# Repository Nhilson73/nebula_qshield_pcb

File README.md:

# Nebula Q-Shield® PCB

**Precision Fermentation Monitor** — PCB shield de 4 capas para el Arduino UNO Q, con sensores de fermentación, control de actuadores, HMI UART y trazabilidad integrada al ecosistema Nebula.

Built by [Cafelium SRL](https://github.com/Nhilson73) · Dominican Republic

> **Parte del ecosistema [Nebula Q-Shield — Arduino App Lab](https://github.com/Nhilson73/Nebula_ArduinoAPPLab_UNOQ)**
>
> **Awards:** I+D Lab INDOTEL 2025 · CREE Banreservas 2026 · Pitch4FUN 2026
>
> **Firmware source of truth:** [`Nhilson73/Nebula_ArduinoAPPLab_UNOQ`](https://github.com/Nhilson73/Nebula_ArduinoAPPLab_UNOQ). No usar `Nebula_UNOQ_ArduinoIDE_Core` para validaciones de pinout/hardware.
>
> **Estado actual (2026-08-12):** esquemático validado (ERC 0 violaciones), PCB en KiCad 10.0.5, factor de forma UNO Q inmutable, dimensiones **150 mm × 120 mm** (se amplió el ancho para la propuesta de placement de Gemini Spark), Fase 4 de potencia completa y Fase 5/6 de ruteo en progreso: DRC 0 violaciones, 72 nets desconectados restantes. Se ajustó `Signal_Default` a vía mínima 0.5/0.2 mm para mejorar conectividad GND. Ver `docs/INSIGHT_FABRICATION_ROADMAP.md`.

---

## ¿Qué es el Q-Shield®?

El Q-Shield® es un **PCB shield de 4 capas** que se monta sobre el Arduino UNO Q (STM32U585 MCU + Qualcomm QRB2210 MPU), convirtiendo la placa en un sistema completo de monitoreo y control de fermentación para café y cacao de especialidad.

Se fabrica como **una sola PCB** para los tres tiers. La diferencia entre tiers se logra poblando o dejando en DNP ciertos componentes; el firmware selecciona el tier en tiempo de compilación.

```
┌──────────────────────────────────────────────────────────────────┐
│                    NEBULA Q-SHIELD® PCB v1.0                     │
│                                                                  │
│  ┌──────────────┐  ┌──────────────┐  ┌──────────────────────┐   │
│  │ POTENCIA     │  │  ANALÓGICO    │  │     DIGITAL          │   │
│  │              │  │              │  │                      │   │
│  │ 12 V input   │  │ pH  (A0)     │  │ I2C bus (D20/D21)    │   │
│  │ Buck 12→5 V  │  │ ORP (A1)     │  │ HX711 (D2/D3)        │   │
│  │ LDO 5→3.3 V  │  │ Temp (A2)    │  │ GPS + RTC (I2C)      │   │
│  │ TVS + PTC    │  │ CO2 (A4)     │  │ RS485 bridge (Sig.)  │   │
│  │ Schottky     │  │ DO  (A5)     │  │ HMI UART             │   │
│  └──────────────┘  └──────────────┘  └──────────────────────┘   │
│                                                                  │
│  ┌──────────────────────────────────────────────────────────┐   │
│  │  ACTUADORES (opto-aislados) — Insight+                  │   │
│  │  Recirculación · Solenoide gas · Chiller                 │   │
│  └──────────────────────────────────────────────────────────┘   │
│                                                                  │
│  ┌──────────────────────────────────────────────────────────┐   │
│  │  CONECTOR ARDUINO UNO Q / R3 (32-pin shield header)      │   │
│  └──────────────────────────────────────────────────────────┘   │
└──────────────────────────────────────────────────────────────────┘
```

---

## Hardware Tier Model

Una sola PCB para los 3 tiers — los componentes no poblados (DNP) se seleccionan en fabricación:

| Tier | Sensores / Funciones | Actuadores | Placements poblados |
|------|----------------------|-----------|---------------------|
| **Essential®** | GPS (altitud), RTC/timestamp, temperatura, pH, ORP, HMI | — | 88 / 163 |
| **Insight®** | Essential + CO₂ (presión), DO, celdas de carga, I2C bus D20/D21 | Recirculación, solenoide gas, chiller | 137 / 163 |
| **Signature®** | Insight + densidad celular total (TCD) + activa (ACD) Hamilton vía RS485 | Igual que Insight | 146 / 163 |

- Convención DNP en el campo `DNP`: lista los tiers en los que el componente **no** se pobla.
- Canal de humedad y válvula PWM de gas quedan eliminados/DNP en todos los tiers.
- El pinout detallado de `J21` está en `docs/INSIGHT_FABRICATION_ROADMAP.md`.

---

## Componentes principales

| # | Componente | Interfaz | Tier |
|---|-----------|----------|------|
| 1 | Sensor pH | Analógico A0 / I2C EZO | Essential+ |
| 2 | Sensor ORP | Analógico A1 / I2C EZO | Essential+ |
| 3 | Sensor temperatura | Analógico A2 | Essential+ |
| 4 | GPS u-blox SAM-M8Q (altitud por GPS) | I2C 0x42 | Essential+ |
| 5 | RTC DS3231 | I2C 0x68 | Essential+ |
| 6 | HMI UART 5" (Nextion/Stone/DWIN) | UART TX/RX | Todos |
| 7 | Celdas de carga + HX711 | Digital D2/D3 | Insight+ |
| 8 | Transductor presión CO₂ | Analógico A4 | Insight+ |
| 9 | Sensor oxígeno disuelto (DO) | Analógico A5 | Insight+ |
| 10 | Driver recirculación (half-bridge) | PWM/DIR D5/D6 | Insight+ |
| 11 | Solenoide gas CO₂/H₂ | GPIO D7 | Insight+ |
| 12 | Chiller (relé opto-aislado) | GPIO D8 | Insight+ |
| 13 | Sensores Hamilton TCD + ACD | RS485/Modbus | Signature |

---

## Diseño 100% Foolproof — 7 Capas de Protección

```
┌─────────────────────────────────────────────────────────┐
│  7. Firmware failsafe (watchdog, store-forward)         │
│  ┌─────────────────────────────────────────────────┐   │
│  │  6. Aislamiento galvánico (ISO7721, PC817)      │   │
│  │  ┌─────────────────────────────────────────┐   │   │
│  │  │  5. Protección térmica (shutdown auto)  │   │   │
│  │  │  ┌─────────────────────────────────┐   │   │   │
│  │  │  │  4. Limitación corriente (PTC)  │   │   │   │
│  │  │  │  ┌─────────────────────────┐   │   │   │   │
│  │  │  │  │  3. ESD/TVS (±8kV)      │   │   │   │   │
│  │  │  │  │  ┌─────────────────┐   │   │   │   │   │
│  │  │  │  │  │  2. Polaridad   │   │   │   │   │   │
│  │  │  │  │  │  ┌─────────┐   │   │   │   │   │   │
│  │  │  │  │  │  │1. Mecán.│   │   │   │   │   │   │
│  │  │  │  │  │  └─────────┘   │   │   │   │   │   │
│  │  │  │  │  └─────────────────┘   │   │   │   │   │
│  │  │  │  └─────────────────────────┘   │   │   │   │
│  │  │  └─────────────────────────────────┘   │   │   │
│  │  └─────────────────────────────────────────┘   │   │
│  └─────────────────────────────────────────────────┘   │
└─────────────────────────────────────────────────────────┘
```

- **Conectores keyed** — Físicamente imposible conectar al revés
- **Schottky SS34** — Protección polaridad inversa sin daño
- **TVS ESD IEC 61000-4-2 Level 4** — ±8 kV contacto, ±15 kV aire
- **PTC recuperable** — Auto-reset después de cortocircuito
- **Thermal shutdown** — Reguladores se apagan a 85°C y se recuperan
- **Opto-aislamiento** — MCU aislado de actuadores de potencia
- **Watchdog dual** — TPS3823 externo (1.6s) + IWDG interno (8s), poblado en TODOS los tiers
- **Aislamiento galvánico on-board** — SN6501 + AMC1301/ISO1541 por canal húmedo (pH, ORP, DO)

---

## Cumplimiento Normativo Europeo

| Directiva | Norma | Estado |
|-----------|-------|--------|
| **EMC** (2014/30/EU) | EN 55032 Clase B, EN 61000-4-2/3/4/5/6 | Diseñado |
| **RoHS 3** (2011/65/EU + 2015/863) | Soldadura SAC305, ENIG, sin Pb/Hg/Cd | Especificado |
| **WEEE** (2012/19/EU) | Categoría 6, registro por país | Pendiente registro |
| **RED** (2014/53/EU) | WiFi/BT via Arduino UNO Q cert. | Verificar con Arduino |
| **REACH** ((EC) 1907/2006) | Verificación SVHC proveedores | Pendiente |
| **Marcado CE** | Declaración de Conformidad | Post-ensayos |

---

## Estructura del Repositorio

```
nebula_qshield_pcb/
├── README.md                          # Este documento
├── .gitignore                         # Exclusiones KiCad/OS
│
├── docs/                              # Documentación de ingeniería
│   ├── 01_PCB_ARCHITECTURE.md         # Arquitectura completa del PCB
│   ├── 02_FOOLPROOF_DESIGN.md         # Diseño 100% Foolproof (7 capas)
│   ├── 03_EU_COMPLIANCE.md            # Cumplimiento normativo europeo
│   ├── 04_BOM_PRODUCTION.md           # BOM con part numbers Digi-Key/Mouser
│   ├── 05_POWER_BUDGET.md             # Análisis de presupuesto de potencia
│   ├── 06_PCB_LAYOUT_STACKUP.md       # Guías de layout y stackup 4 capas
│   ├── 07_KICAD_NETLIST.md            # Netlist KiCad y definiciones
│   ├── 08_MECHANICAL_ANALYSIS.md      # Análisis mecánico y compactación
│   ├── INSIGHT_FABRICATION_ROADMAP.md # Hoja de ruta JLCPCB para Insight
│   ├── UNO_Q_FORM_FACTOR.md           # Referencia inmutable del factor de forma UNO Q
│   ├── KICAD10_SSH_SETUP.md           # Guía SSH para clonar desde KiCad 10
│   └── DOCUMENTATION_UPDATE_AUDIT.md  # Auditoría de docs por actualizar
│
├── kicad/                             # Proyecto KiCad 10.0.5
│   ├── nebula_qshield.kicad_pro       # Proyecto principal
│   ├── nebula_qshield.kicad_sch       # Esquemático raíz (jerárquico)
│   ├── nebula_qshield.kicad_pcb       # Layout PCB (en progreso)
│   ├── power_management.kicad_sch     # Sub-hoja: reguladores y protección
│   ├── analog_acquisition.kicad_sch   # Sub-hoja: canales analógicos
│   ├── digital_i2c.kicad_sch          # Sub-hoja: bus I2C, HX711, RS485 bridge
│   ├── actuator_drivers.kicad_sch     # Sub-hoja: drivers de actuadores
│   ├── hmi_connectors.kicad_sch       # Sub-hoja: HMI UART y J21
│   ├── lib/                           # Librerías de símbolos y footprints
│   ├── production/                    # Salidas de fabricación
│   └── UNO_Q_rearchitecture_report.md # Reporte de re-arquitectura UNO Q
│
├── hardware/                          # Diseño mecánico
│   ├── enclosure/                     # Carcasa/enclosure IP54
│   └── cables/                        # Especificaciones de cables
│
├── test/                              # Testing y validación
│   ├── hil/                           # Hardware-in-the-Loop tests
│   └── validation/                    # Reportes de validación
│
└── tools/                             # Scripts Python de automatización
    ├── tier_counts.py                 # Conteos de componentes por tier
    ├── apply_tier_dnp4.py            # Aplicar propiedades DNP por tier
    ├── compare_pcb_to_netlist.py      # Verificar paridad PCB/netlist
    └── update_tier_comments.py       # Actualizar comentarios de tier
```

### Esquemáticos Jerárquicos

```
nebula_qshield.kicad_sch (raíz)
├── power_management.kicad_sch     → 12V protección, Buck 5V, LDO 3.3V, TPS3823 watchdog
├── analog_acquisition.kicad_sch   → pH/ORP/Temp/CO₂/DO + aislamiento galvánico
├── digital_i2c.kicad_sch          → I2C (D20/D21), HX711, RS485 Modbus bridge (Signature)
├── actuator_drivers.kicad_sch     → Recirculación, solenoide gas, chiller
└── hmi_connectors.kicad_sch       → HMI UART y shield header J21
```

---

## Especificaciones Técnicas

| Parámetro | Valor |
|-----------|-------|
| **Dimensiones** | 125 mm × 120 mm (factor de forma Arduino UNO Q inmutable; el tamaño exterior puede variar) |
| **Capas** | 4 (Signal–GND–Power–Signal) |
| **Material** | FR-4 Tg 170°C |
| **Acabado** | ENIG (RoHS) |
| **Cobre** | 1 oz (35 μm) todas las capas |
| **Temperatura operativa** | -10°C a +55°C |
| **Alimentación** | 12V DC (Essential: 2A, Insight: 3A, Signature: 8A) |
| **Placements totales** | 163 (88 Essential / 137 Insight / 146 Signature) |
| **KiCad** | 10.0.5 |
| **IPC Class** | Clase 2 |

---

## Presupuesto de Potencia

| Tier | Potencia continua | Fuente recomendada |
|------|-------------------|-------------------|
| Essential® | 11 W | 12V 2A (24W) |
| Insight® | 23 W | 12V 3A (36W) |
| Signature® | 65 W | 12V 8A (96W) |

---

## Getting Started

### Requisitos

- [KiCad 10.0.5](https://www.kicad.org/download/)
- [Python 3.11+](https://www.python.org/) (para scripts de BOM/CPL)
- Cuenta GitHub con acceso al repositorio

### Clonar el proyecto

Opción A — terminal:

```bash
git clone git@github.com:Nhilson73/nebula_qshield_pcb.git
cd nebula_qshield_pcb/kicad
# Abrir nebula_qshield.kicad_pro con KiCad 10
```

Opción B — desde KiCad 10:

Ver `docs/KICAD10_SSH_SETUP.md` para configurar SSH y clonar directamente desde `File → Clone Project from Git Repository`.

### Validación del diseño

```bash
# ERC
docker run --rm -v "$PWD:/workspace" kicad/kicad:10.0.5 \
  kicad-cli sch erc --severity-all \
  /workspace/kicad/nebula_qshield.kicad_sch

# DRC error-level
docker run --rm -v "$PWD:/workspace" kicad/kicad:10.0.5 \
  kicad-cli pcb drc --severity-error \
  /workspace/kicad/nebula_qshield.kicad_pcb

# Paridad PCB/netlist (exportar primero el netlist XML)
docker run --rm -v "$PWD:/workspace" kicad/kicad:10.0.5 \
  kicad-cli sch export netlist --format kicadxml \
  -o /workspace/kicad/uno_q.xml /workspace/kicad/nebula_qshield.kicad_sch

docker run --rm -v "$PWD:/workspace" kicad/kicad:10.0.5 \
  python3 /workspace/tools/compare_pcb_to_netlist.py
```

### Generar archivos de fabricación

Desde KiCad 10:

```
File → Plot → Gerber
File → Fabrication Outputs → Drill Files
File → Fabrication Outputs → BOM
File → Fabrication Outputs → Footprint Position File
```

Los parámetros de fabricación JLCPCB están en `docs/INSIGHT_FABRICATION_ROADMAP.md` y `docs/04_BOM_PRODUCTION.md`.

---

## Pinout J21 de referencia (Insight)

| Pin | Función | Net |
|-----|---------|-----|
| 1 | BOOT | NC |
| 2 | IOREF | NC |
| 3 | ~RESET | `/MCU_NRST` |
| 4 | +3V3 | `/3V3_RAIL` |
| 5 | +5V | `/5V_RAIL` |
| 6 | GND | `GND` |
| 7 | GND2 | `GND` |
| 8 | VIN | `/12V_RAIL` |
| 9 | A0/D14 | `/PH_ADC` |
| 10 | A1/D15 | `/ORP_ADC` |
| 11 | A2/D16 | `/TEMP_ADC` |
| 12 | A3/D17 | `/HUM_ADC` — DNP all tiers |
| 13 | A4/D18 | `/CO2_ADC` |
| 14 | A5/D19 | `/DO_ADC` |
| 15 | D0 | `/HMI_RX` |
| 16 | D1 | `/HMI_TX` |
| 17 | D2 | `/HX711_DOUT` |
| 18 | D3 | `/HX711_SCK` |
| 19 | D4 | `/MCU_WDI` |
| 20 | D5 | `/PUMP_PWM` |
| 21 | D6 | `/PUMP_DIR` |
| 22 | D7 | `/CO2_SOL_CTL` |
| 23 | D8 | `/CHILLER_CTL` |
| 24 | D9 | `/CO2_PWM` — DNP all tiers |
| 25 | D10 | `/RS485_IRQ` |
| 26 | D11 | NC |
| 27 | D12 | NC |
| 28 | D13 | `/LED_STATUS` |
| 29 | GND | `GND` |
| 30 | AREF | NC |
| 31 | D20/SDA | `/I2C_SDA` |
| 32 | D21/SCL | `/I2C_SCL` |

El pinout completo, mapa de tiers y hoja de ruta de fabricación están en `docs/INSIGHT_FABRICATION_ROADMAP.md`.

---

## Repositorios Relacionados

| Repositorio | Descripción |
|------------|-------------|
| [Nebula_ArduinoAPPLab_UNOQ](https://github.com/Nhilson73/Nebula_ArduinoAPPLab_UNOQ) | Firmware MCU + Software MPU + Servicios Docker + Contratos L2. **Source of truth** para el pinout y lógica del Q-Shield. |
| **nebula_qshield_pcb** (este repo) | PCB shield para Arduino UNO Q (esquemáticos KiCad, BOM, compliance) |

---

## Licencia

Proprietary — Cafelium SRL. All rights reserved.

---

## Team

- **Nhilson** — Lead Architect
- **Drancés** — Co-founder
- **Alfredo** — Co-founder

Powered by the **Nebula Ecosystem™**: Nebula Terra® · Nebula Fermentation® · Nebula Originblok® · Nebula Marketplace®

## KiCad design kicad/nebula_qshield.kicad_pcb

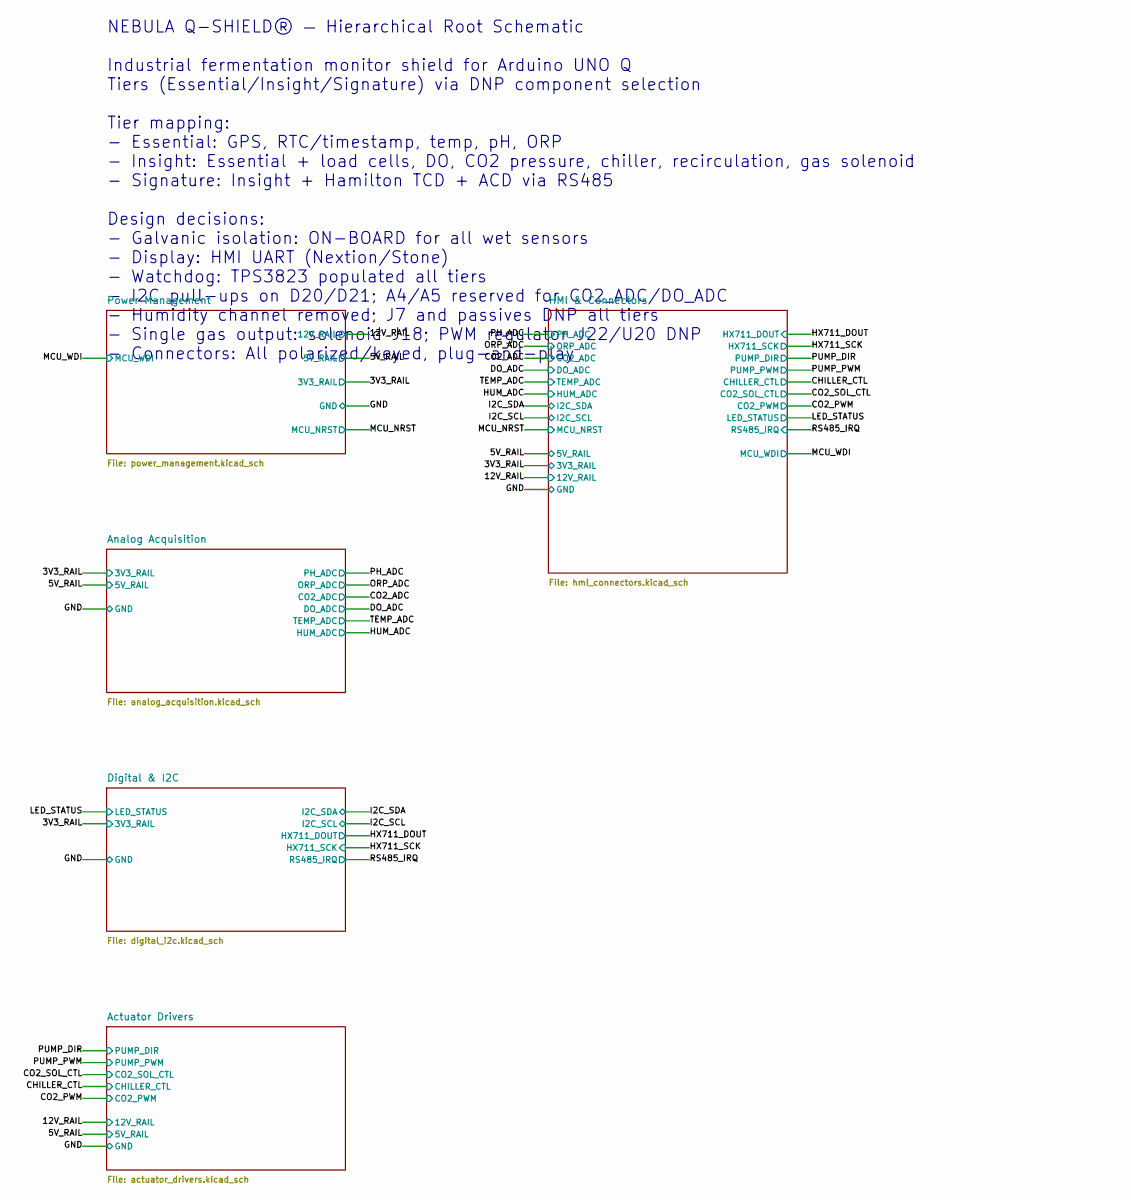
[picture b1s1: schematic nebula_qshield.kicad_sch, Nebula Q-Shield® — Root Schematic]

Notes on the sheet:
NEBULA Q-SHIELD® — Hierarchical Root Schematic Industrial fermentation monitor shield for Arduino UNO Q Tiers (Essential/Insight/Signature) via DNP component selection Tier mapping: - Essential: GPS, RTC/timestamp, temp, pH, ORP - Insight: Essential + load cells, DO, CO2 pressure, chiller, recircul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

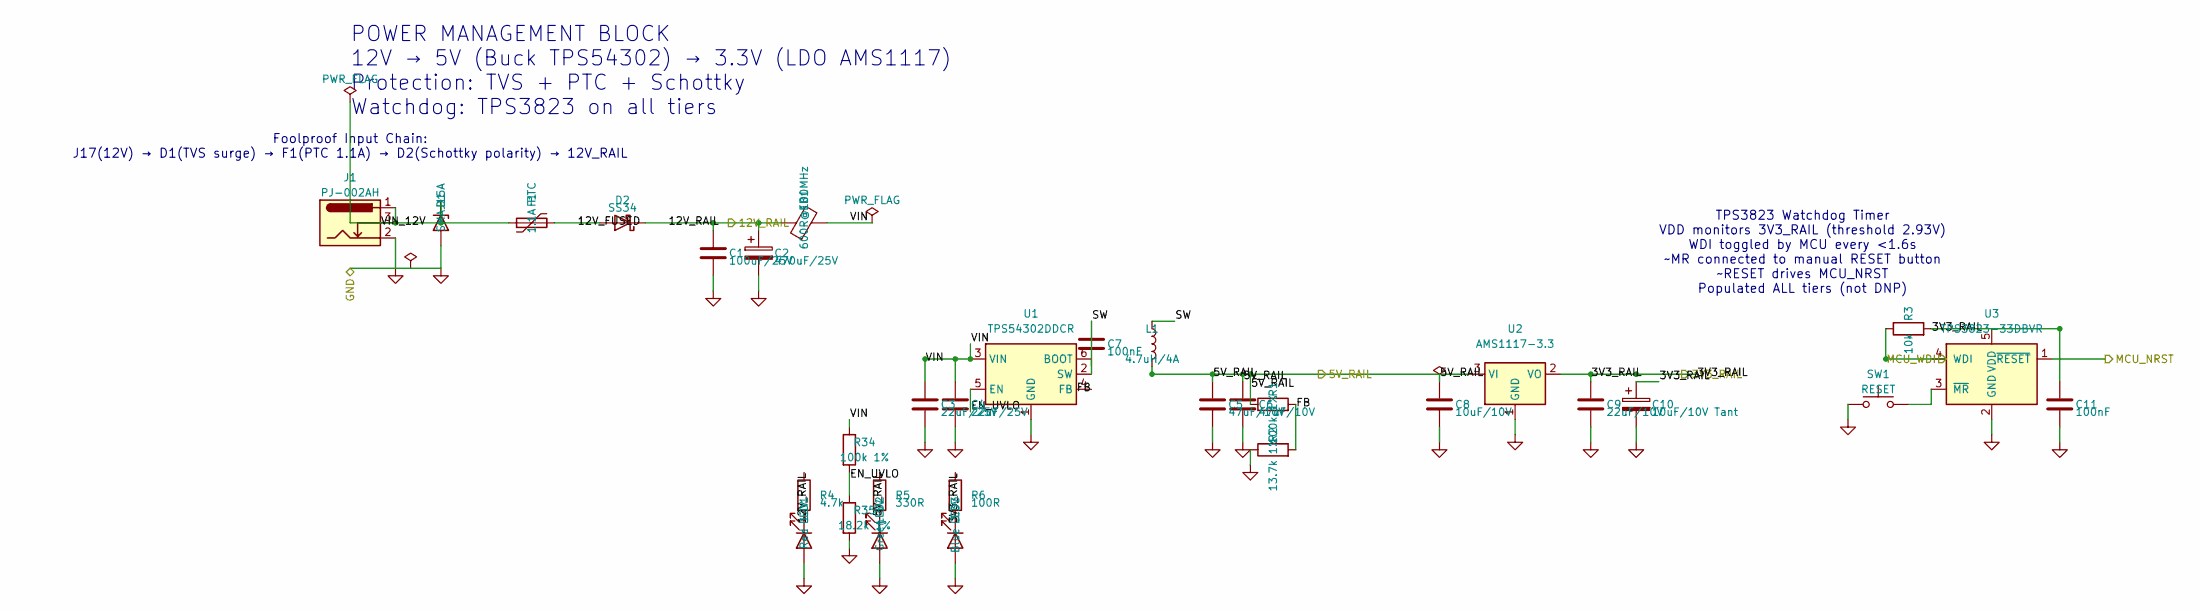
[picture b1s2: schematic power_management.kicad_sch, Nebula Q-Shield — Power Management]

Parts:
C1: 100uF/25V; C_1210_3225Metric; MPN GRM32ER61E107ME20L
C2: 470uF/25V; CP_Radial_D10.0mm_P5.00mm; MPN UCD1E471MNL1GS
C3, C4: 22uF/25V; C_0805_2012Metric; MPN GRM21BR61E226ME44L
C5, C6: 47uF/10V; C_0805_2012Metric; MPN GRM21BR61A476ME15L
C7, C11: 100nF; C_0402_1005Metric
C8: 10uF/10V; C_0805_2012Metric; MPN GRM21BR61A106KE19L
C9: 22uF/10V; C_0805_2012Metric; MPN GRM21BR61A226ME44L
C10: 10uF/10V Tant; C_1206_3216Metric; MPN T491A106M010AT
D1: SMAJ15A; D_SMA; MPN SMAJ15A; Digi-Key_PN SMAJ15ALFCT-ND
D2: SS34; D_SMA; MPN SS34; Digi-Key_PN SS34-E3/57TCT-ND
F1: 1.1A PTC; Fuse_1812_4532Metric; MPN MF-MSMF110/24X-2; Digi-Key_PN MF-MSMF110/24X-2CT-ND
FB1: 600R@100MHz; L_1206_3216Metric; MPN BLM31PG601SN1L; Digi-Key_PN 490-5222-1-ND
J1: PJ-002AH; BarrelJack_Horizontal; MPN PJ-002AH; Digi-Key_PN CP-002AH-ND
L1: 4.7uH/4A; L_Taiyo-Yuden_NR-40xx; MPN 744043004700; Digi-Key_PN 732-1260-1-ND
LED1: Red 12V; LED_0603_1608Metric; MPN 150060RS75000
LED2: Green 5V; LED_0603_1608Metric; MPN 150060GS75000
LED3: Blue 3.3V; LED_0603_1608Metric; MPN 150060BS75000
R1, R34: 100k 1%; R_0402_1005Metric; MPN CRCW0402100KFKED
R2: 13.7k 1%; R_0402_1005Metric; MPN CRCW040213K7FKED
R3: 10k; R_0402_1005Metric
R4: 4.7k; R_0402_1005Metric
R5: 330R; R_0402_1005Metric
R6: 100R; R_0402_1005Metric
R35: 18.2k 1%; R_0402_1005Metric; MPN CRCW040218K2FKED
SW1: RESET; SW_SPST_TL3342
U1: TPS54302DDCR; SOT-23-6; MPN TPS54302DDCR; Digi-Key_PN 296-50420-1-ND
U2: AMS1117-3.3; SOT-223-3_TabPin2; MPN AMS1117-3.3
U3: TPS3823-33DBVR; SOT-23-5; Digi-Key_PN 296-34371-1-ND

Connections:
/3V3_RAIL: C9.1, C10.1, C11.1, R3.2, R6.1, U2.2 (VO), U3.5 (VDD); also elsewhere on the board
/5V_RAIL: C5.1, C6.1, C8.1, L1.2, R1.1, R5.1, U2.3 (VI); also elsewhere on the board
/12V_RAIL: C1.1, C2.1, D2.1 (K), FB1.1, R4.1; also elsewhere on the board
/MCU_NRST: U3.1 (~RESET); also elsewhere on the board
/MCU_WDI: R3.1, U3.4 (WDI); also elsewhere on the board
/Power Management/12V_FUSED: D2.2 (A), F1.2
/Power Management/EN_UVLO: R34.2, R35.1, U1.5 (EN)
/Power Management/FB: R1.2, R2.2, U1.4 (FB)
/Power Management/SW: C7.1, L1.1, U1.2 (SW)
/Power Management/VIN: C3.1, C4.1, FB1.2, R34.1, U1.3 (VIN)
/Power Management/VIN_12V: D1.1 (A1), F1.1, J1.1, J1.3
GND: C1.2, C2.2, C3.2, C4.2, C5.2, C6.2, C8.2, C9.2, C10.2, C11.2, D1.2 (A2), J1.2, LED1.2 (A), LED2.2 (A), LED3.2 (A), R2.1, R35.2, SW1.1, U1.1 (GND), U2.1 (GND), U3.2 (GND); also elsewhere on the board
unnamed: LED1.1 (K), R4.2
unnamed: LED2.1 (K), R5.2
unnamed: LED3.1 (K), R6.2
unnamed: C7.2, U1.6 (BOOT)
unnamed: SW1.2, U3.3 (~MR)

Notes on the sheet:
POWER MANAGEMENT BLOCK 12V → 5V (Buck TPS54302) → 3.3V (LDO AMS1117) Protection: TVS + PTC + Schottky Watchdog: TPS3823 on all tiers
Foolproof Input Chain: J17(12V) → D1(TVS surge) → F1(PTC 1.1A) → D2(Schottky polarity) → 12V_RAIL
TPS3823 Watchdog Timer VDD monitors 3V3_RAIL (threshold 2.93V) WDI toggled by MCU every <1.6s ~MR connected to manual RESET button ~RESET drives MCU_NRST Populated ALL tiers (not DNP)

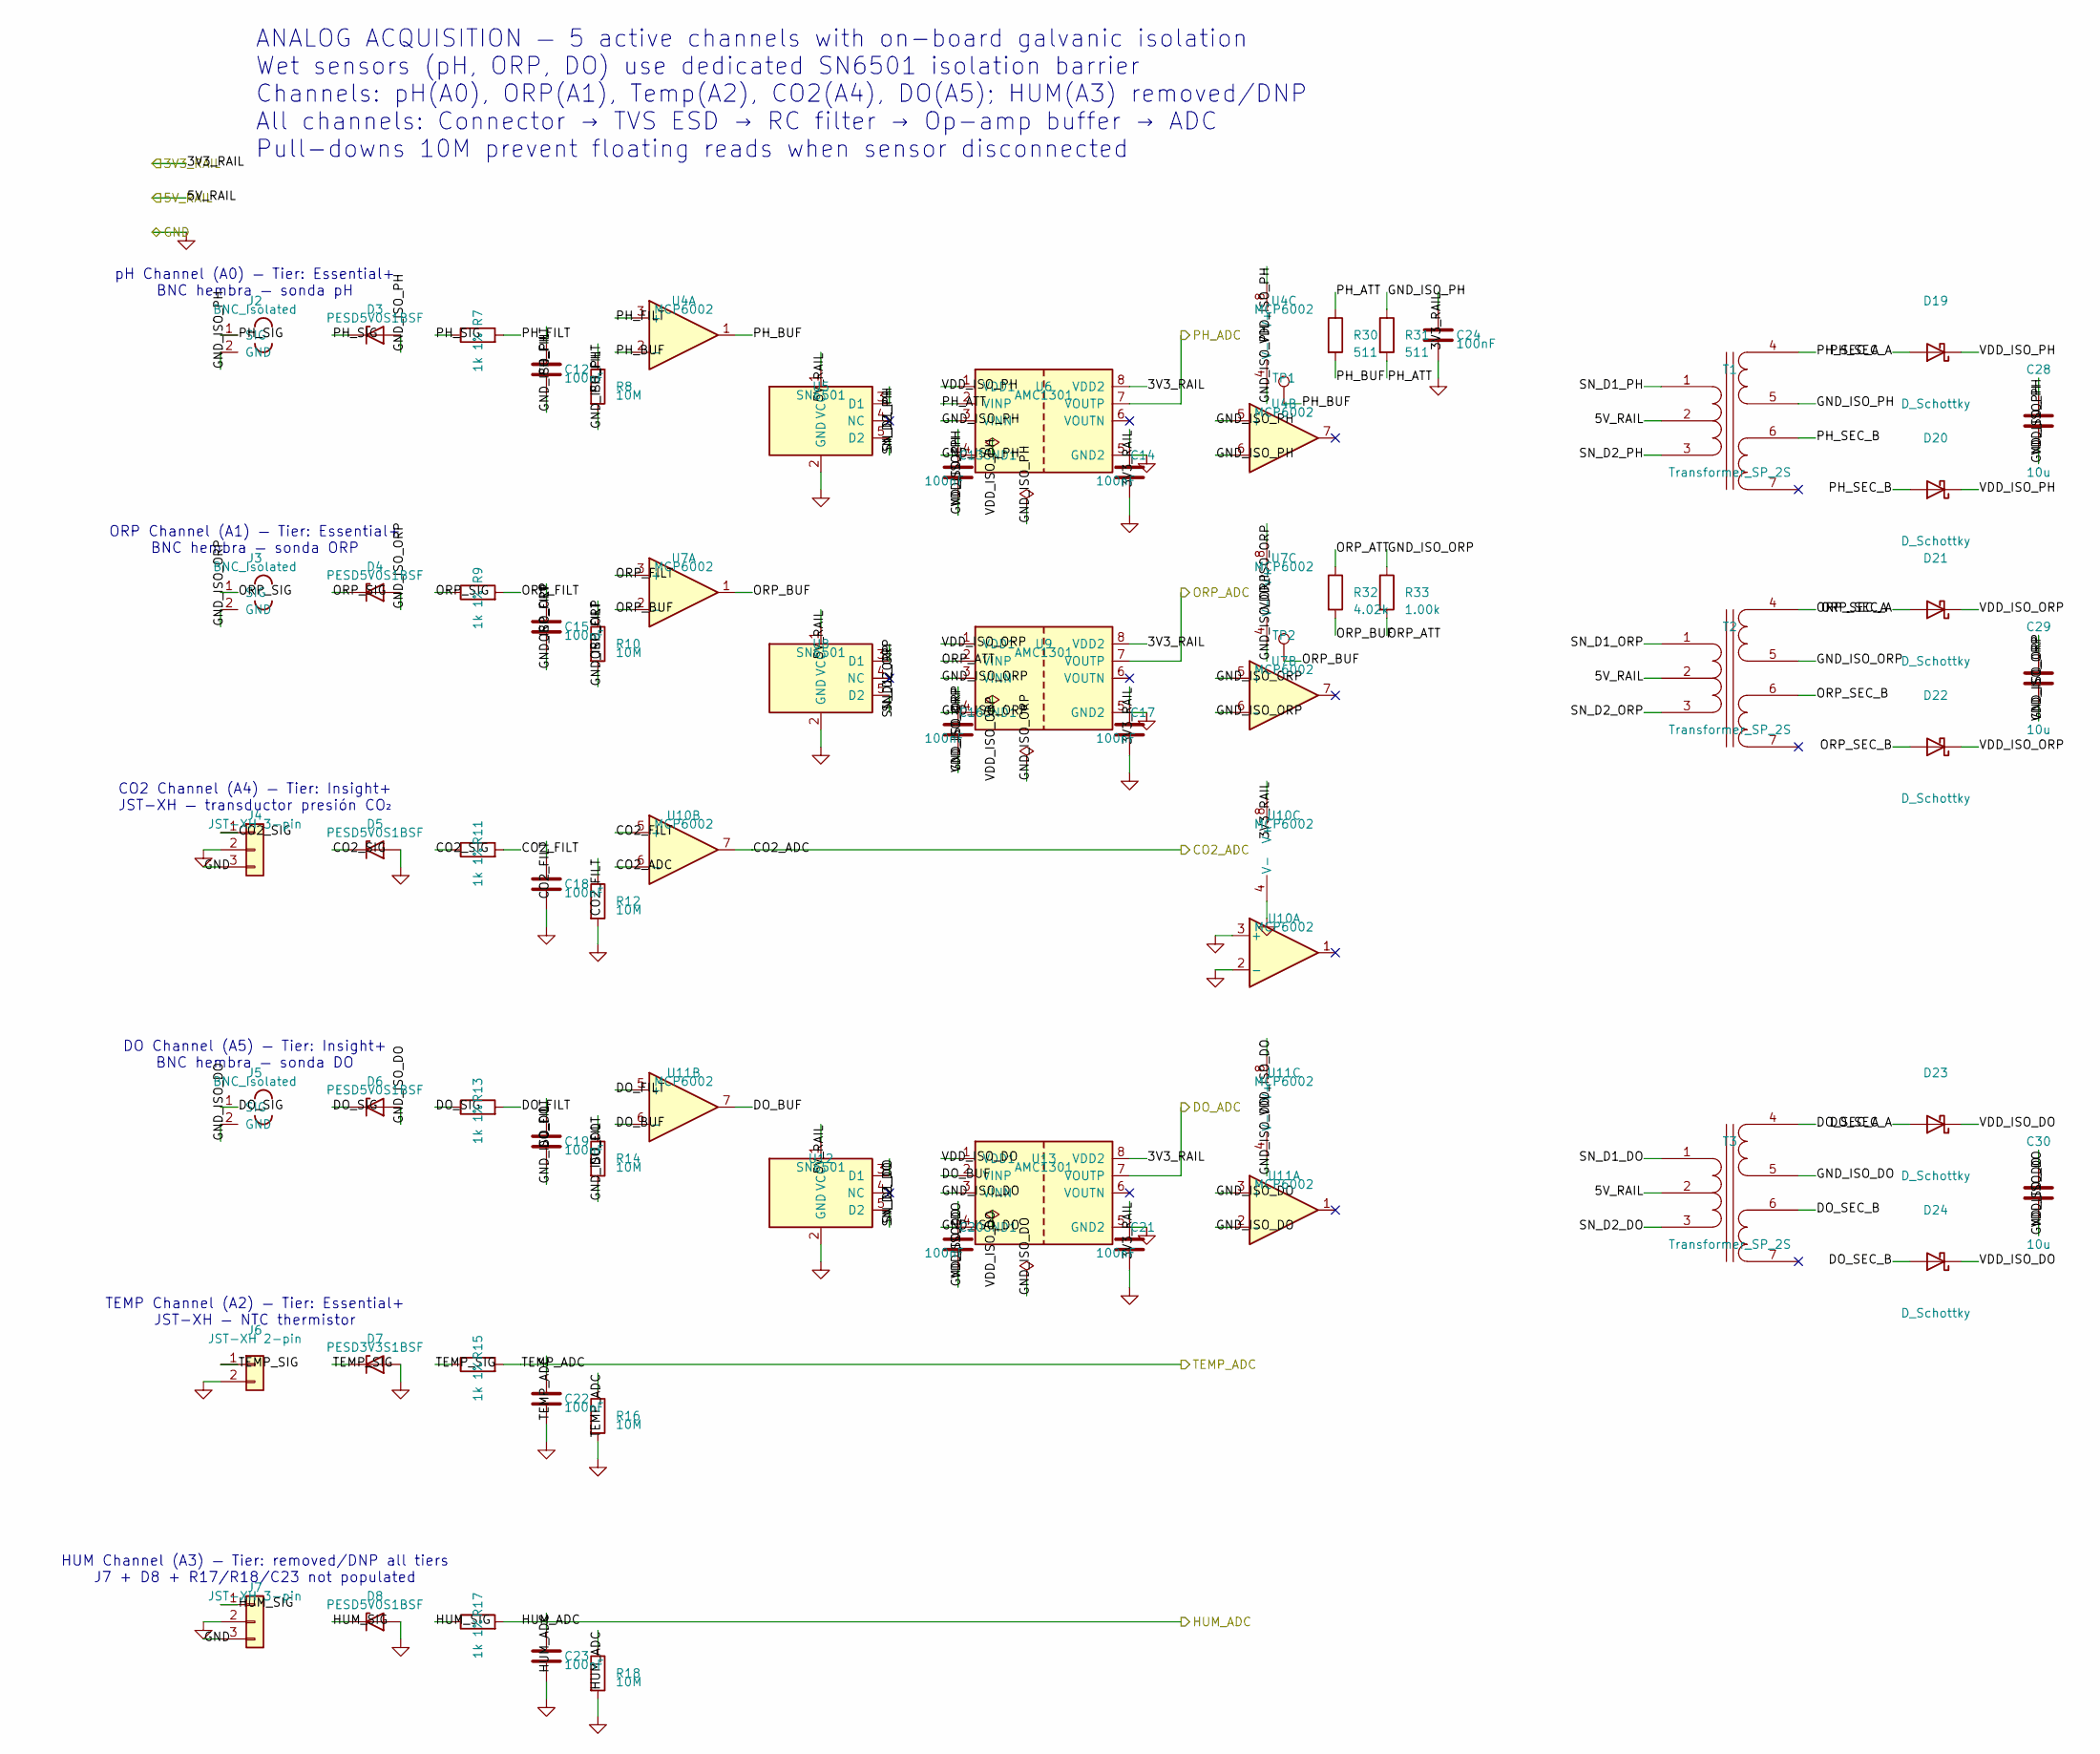
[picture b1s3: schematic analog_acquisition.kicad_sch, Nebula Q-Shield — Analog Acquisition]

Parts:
C12, C13, C14, C15, C16, C17, C18, C19, C20, C21, C22, C23, C24: 100nF; C_0402_1005Metric
C28, C29, C30: 10u; C_0805_2012Metric; MPN GRM21BR61C106KE15L
D3, D4, D5, D6, D8: PESD5V0S1BSF; D_SOD-323F; MPN PESD5V0S1BSF; Digi-Key_PN 568-13204-1-ND
D7: PESD3V3S1BSF; D_SOD-323F; MPN PESD3V3S1BSF; Digi-Key_PN 568-13206-1-ND
D19, D20, D21, D22, D23, D24: D_Schottky; D_SOD-123; MPN BAT54,115
J2, J3, J5: BNC_Isolated; BNC_Panel_Mount_Isolated
J4, J7: JST-XH 3-pin; JST_XH_B3B-XH-A_1x03_P2.50mm_Vertical
J6: JST-XH 2-pin; JST_XH_B2B-XH-A_1x02_P2.50mm_Vertical
R7, R9, R11, R13, R15, R17: 1k 1%; R_0402_1005Metric; MPN CRCW04021K00FKED
R8, R10, R12, R14, R16, R18: 10M; R_0402_1005Metric
R30, R31: 511; R_0402_1005Metric
R32: 4.02k; R_0402_1005Metric
R33: 1.00k; R_0402_1005Metric
T1, T2, T3: Transformer_SP_2S; Transformer_Wuerth_750315371; MPN 750315371
TP1, TP2: TestPoint; TestPoint_Pad_D1.5mm
U4, U7, U10, U11: MCP6002; SOIC-8_3.9x4.9mm_P1.27mm; MPN MCP6002-I/SN; Digi-Key_PN MCP6002-I/SN-ND
U5, U8, U12: SN6501; SOT-23-5
U6, U9, U13: AMC1301; SOIC-8_3.9x4.9mm_P1.27mm; MPN AMC1301DWVR

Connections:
/3V3_RAIL: C14.1, C17.1, C21.1, C24.1, U6.8 (VDD2), U9.8 (VDD2), U10.8 (V+), U13.8 (VDD2); also elsewhere on the board
/5V_RAIL: T1.2 (PM), T2.2 (PM), T3.2 (PM), U5.1 (VCC), U8.1 (VCC), U12.1 (VCC); also elsewhere on the board
/Analog Acquisition/CO2_FILT: C18.1, R11.2, R12.1, U10.5 (+)
/Analog Acquisition/CO2_SIG: D5.1 (K), J4.1, R11.1
/Analog Acquisition/DO_BUF: U11.6 (-), U11.7, U13.2 (VINP)
/Analog Acquisition/DO_FILT: C19.1, R13.2, R14.1, U11.5 (+)
/Analog Acquisition/DO_SEC_A: D23.2 (A), T3.4 (OUT1A)
/Analog Acquisition/DO_SEC_B: D24.2 (A), T3.6 (OUT2A)
/Analog Acquisition/DO_SIG: D6.1 (K), J5.1 (SIG), R13.1
/Analog Acquisition/GND_ISO_DO: C19.2, C20.2, C30.2, D6.2 (A), J5.2 (GND), R14.2, T3.5 (OUT1B), U11.2 (-), U11.3 (+), U11.4 (V-), U13.3 (VINN), U13.4 (GND1)
/Analog Acquisition/GND_ISO_ORP: C15.2, C16.2, C29.2, D4.2 (A), J3.2 (GND), R10.2, R33.1, T2.5 (OUT1B), U7.4 (V-), U7.5 (+), U7.6 (-), U9.3 (VINN), U9.4 (GND1)
/Analog Acquisition/GND_ISO_PH: C12.2, C13.2, C28.2, D3.2 (A), J2.2 (GND), R8.2, R31.1, T1.5 (OUT1B), U4.4 (V-), U4.5 (+), U4.6 (-), U6.3 (VINN), U6.4 (GND1)
/Analog Acquisition/HUM_SIG: D8.1 (K), J7.1, R17.1
/Analog Acquisition/ORP_ATT: R32.1, R33.2, U9.2 (VINP)
/Analog Acquisition/ORP_BUF: R32.2, TP2.1, U7.1, U7.2 (-)
/Analog Acquisition/ORP_FILT: C15.1, R9.2, R10.1, U7.3 (+)
/Analog Acquisition/ORP_SEC_A: D21.2 (A), T2.4 (OUT1A)
/Analog Acquisition/ORP_SEC_B: D22.2 (A), T2.6 (OUT2A)
/Analog Acquisition/ORP_SIG: D4.1 (K), J3.1 (SIG), R9.1
/Analog Acquisition/PH_ATT: R30.1, R31.2, U6.2 (VINP)
/Analog Acquisition/PH_BUF: R30.2, TP1.1, U4.1, U4.2 (-)
/Analog Acquisition/PH_FILT: C12.1, R7.2, R8.1, U4.3 (+)
/Analog Acquisition/PH_SEC_A: D19.2 (A), T1.4 (OUT1A)
/Analog Acquisition/PH_SEC_B: D20.2 (A), T1.6 (OUT2A)
/Analog Acquisition/PH_SIG: D3.1 (K), J2.1 (SIG), R7.1
/Analog Acquisition/SN_D1_DO: T3.1 (IN+), U12.3 (D1)
/Analog Acquisition/SN_D1_ORP: T2.1 (IN+), U8.3 (D1)
/Analog Acquisition/SN_D1_PH: T1.1 (IN+), U5.3 (D1)
/Analog Acquisition/SN_D2_DO: T3.3 (IN-), U12.5 (D2)
/Analog Acquisition/SN_D2_ORP: T2.3 (IN-), U8.5 (D2)
/Analog Acquisition/SN_D2_PH: T1.3 (IN-), U5.5 (D2)
/Analog Acquisition/TEMP_SIG: D7.1 (K), J6.1, R15.1
/Analog Acquisition/VDD_ISO_DO: C20.1, C30.1, D23.1 (K), D24.1 (K), U11.8 (V+), U13.1 (VDD1)
/Analog Acquisition/VDD_ISO_ORP: C16.1, C29.1, D21.1 (K), D22.1 (K), U7.8 (V+), U9.1 (VDD1)
/Analog Acquisition/VDD_ISO_PH: C13.1, C28.1, D19.1 (K), D20.1 (K), U4.8 (V+), U6.1 (VDD1)
/CO2_ADC: U10.6 (-), U10.7; also elsewhere on the board
/DO_ADC: U13.7 (VOUTP); also elsewhere on the board
/HUM_ADC: C23.1, R17.2, R18.1; also elsewhere on the board
/ORP_ADC: U9.7 (VOUTP); also elsewhere on the board
/PH_ADC: U6.7 (VOUTP); also elsewhere on the board
/TEMP_ADC: C22.1, R15.2, R16.1; also elsewhere on the board
GND: C14.2, C17.2, C18.2, C21.2, C22.2, C23.2, C24.2, D5.2 (A), D7.2 (A), D8.2 (A), J4.2, J4.3, J6.2, J7.2, J7.3, R12.2, R16.2, R18.2, U5.2 (GND), U6.5 (GND2), U8.2 (GND), U9.5 (GND2), U10.2 (-), U10.3 (+), U10.4 (V-), U12.2 (GND), U13.5 (GND2); also elsewhere on the board

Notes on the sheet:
pH Channel (A0) — Tier: Essential+ BNC hembra — sonda pH
ORP Channel (A1) — Tier: Essential+ BNC hembra — sonda ORP
CO2 Channel (A4) — Tier: Insight+ JST-XH — transductor presión CO₂
DO Channel (A5) — Tier: Insight+ BNC hembra — sonda DO
TEMP Channel (A2) — Tier: Essential+ JST-XH — NTC thermistor
HUM Channel (A3) — Tier: removed/DNP all tiers J7 + D8 + R17/R18/C23 not populated
ANALOG ACQUISITION — 5 active channels with on-board galvanic isolation Wet sensors (pH, ORP, DO) use dedicated SN6501 isolation barrier Channels: pH(A0), ORP(A1), Temp(A2), CO2(A4), DO(A5); HUM(A3) removed/DNP All channels: Connector → TVS ESD → RC filter → Op-amp buffer → ADC Pull-downs 10M preve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

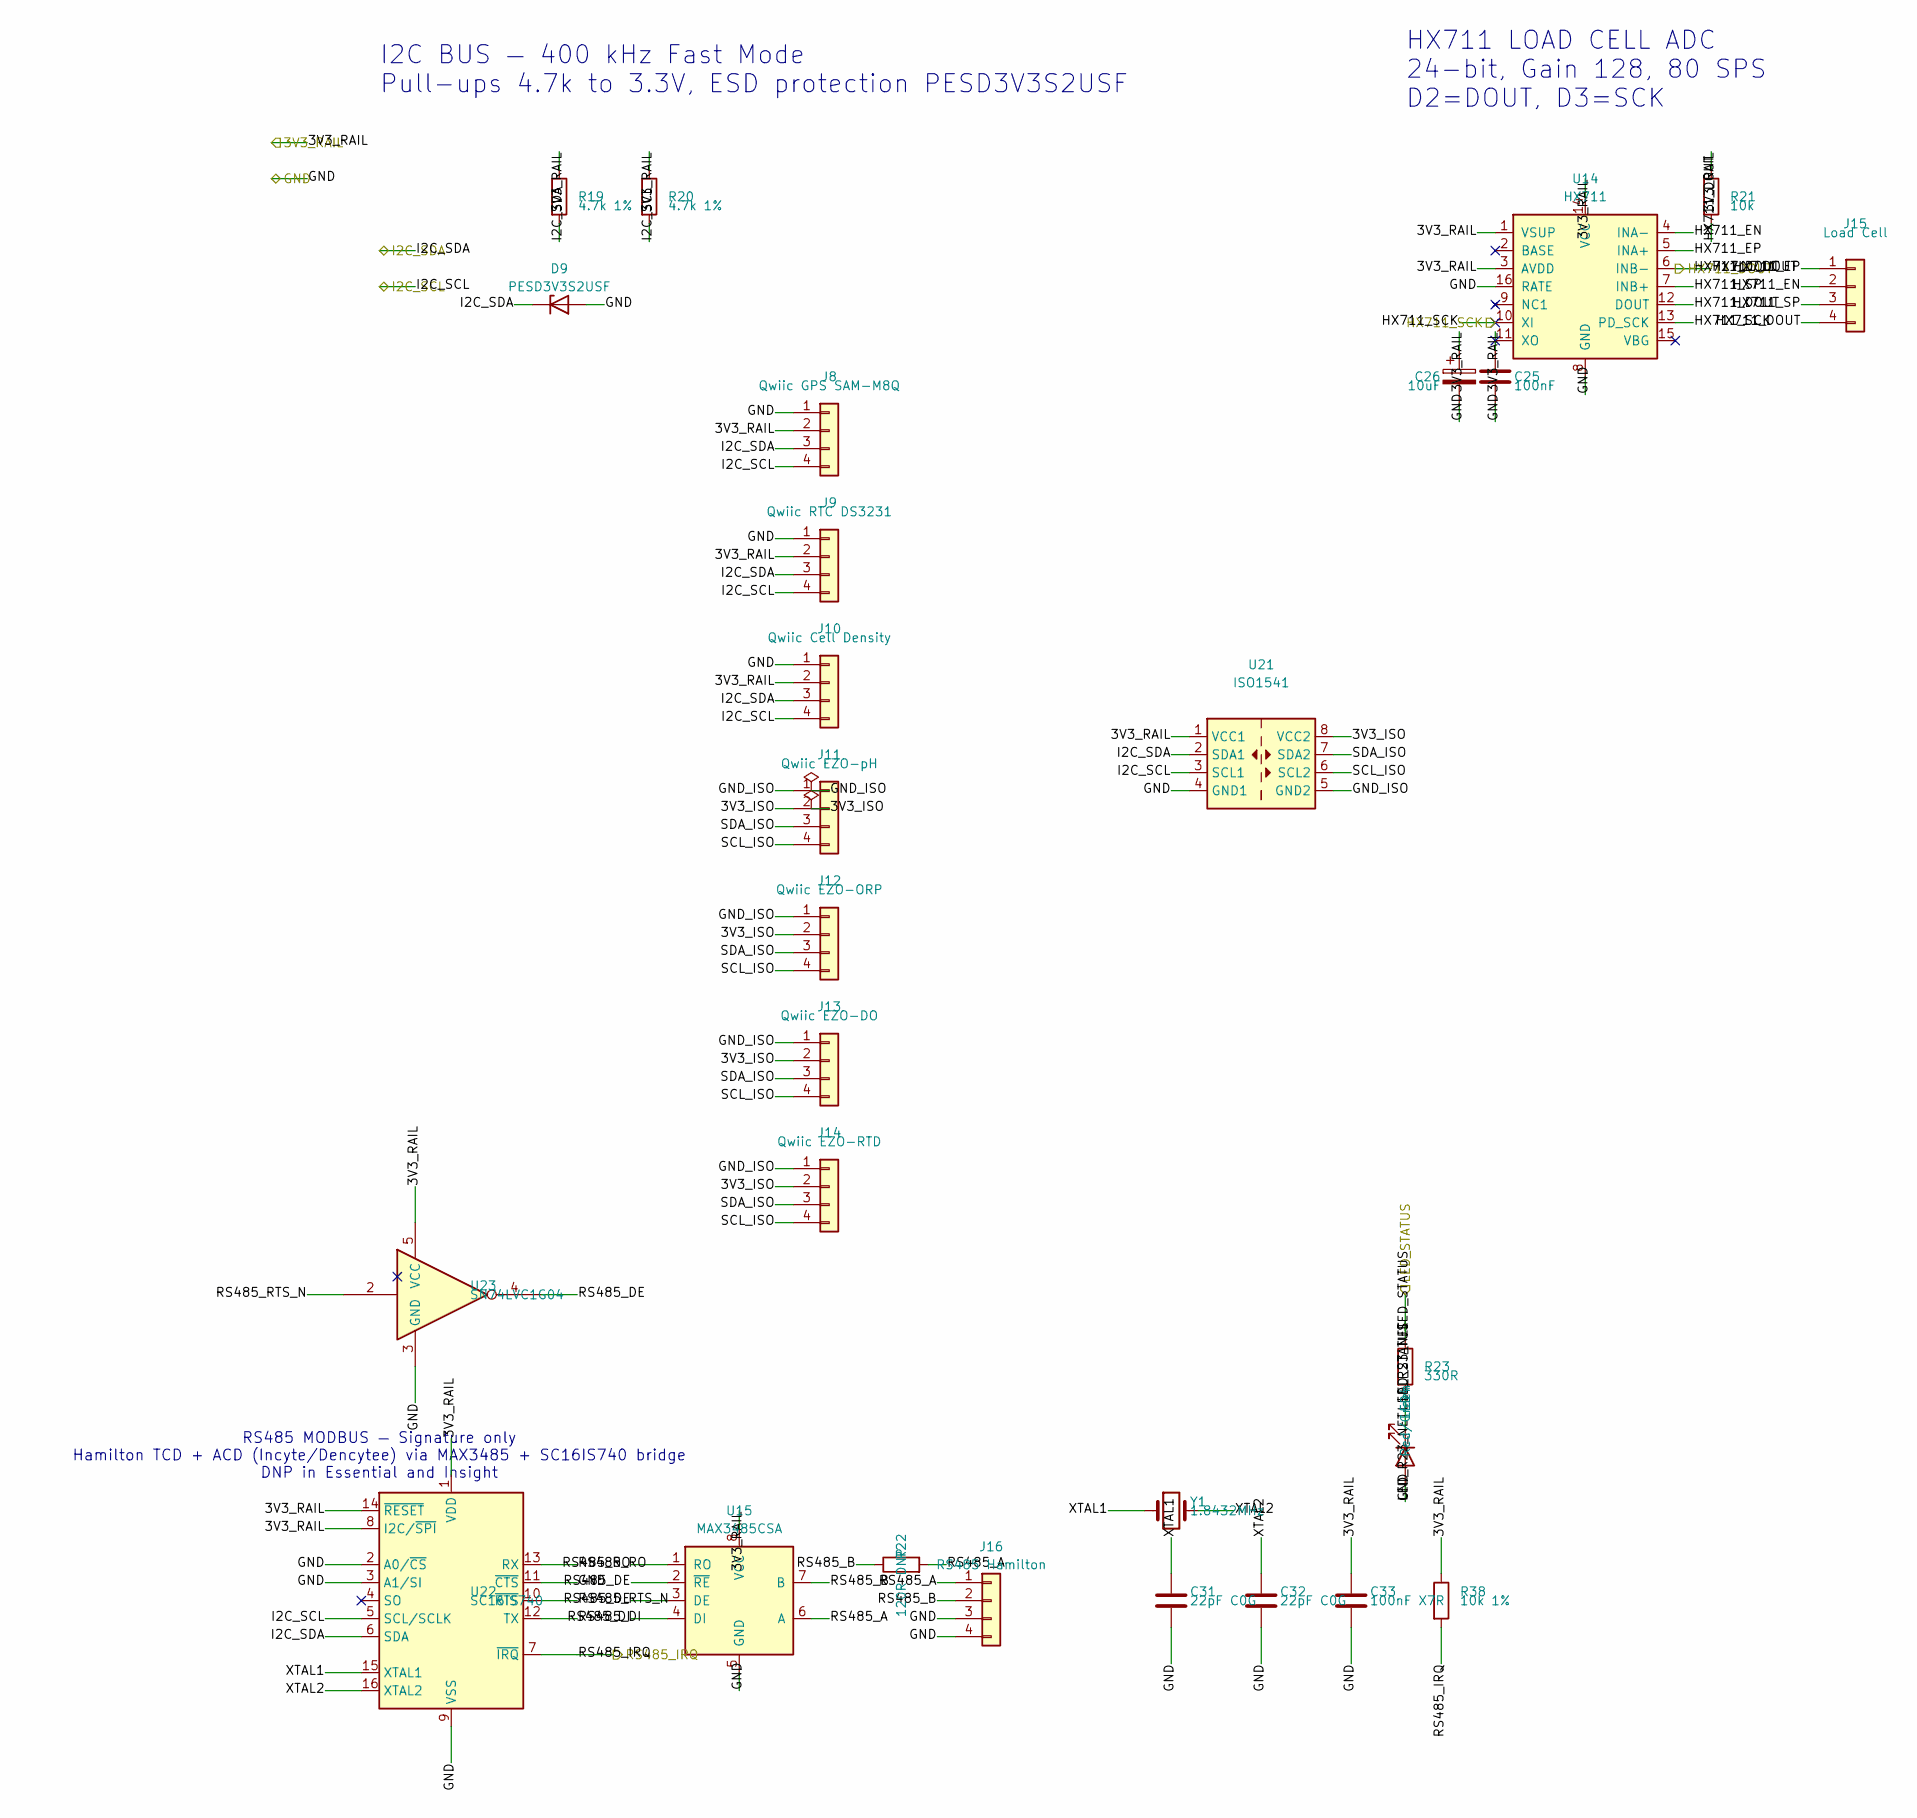
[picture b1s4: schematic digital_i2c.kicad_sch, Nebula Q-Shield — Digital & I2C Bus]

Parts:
C25: 100nF; C_0402_1005Metric
C26: 10uF; C_0805_2012Metric
C31, C32: 22pF C0G; C_0402_1005Metric; MPN CL05C220JB5NNNC; Digi-Key_PN 1276-1013-1-ND
C33: 100nF X7R; C_0402_1005Metric; MPN CL05B104KO5NNNC; Digi-Key_PN 1276-1000-1-ND
D9: PESD3V3S2USF; SOT-23-3; MPN PESD3V3S2USF; Digi-Key_PN 568-13207-1-ND
J8: Qwiic GPS SAM-M8Q; JST_SH_SM04B-SRSS-TB_1x04-1MP_P1.00mm_Horizontal; MPN SM04B-SRSS-TB(LF)(SN); Digi-Key_PN 455-1804-1-ND
J9: Qwiic RTC DS3231; JST_SH_SM04B-SRSS-TB_1x04-1MP_P1.00mm_Horizontal; MPN SM04B-SRSS-TB(LF)(SN); Digi-Key_PN 455-1804-1-ND
J10: Qwiic Cell Density; JST_SH_SM04B-SRSS-TB_1x04-1MP_P1.00mm_Horizontal; MPN SM04B-SRSS-TB(LF)(SN); Digi-Key_PN 455-1804-1-ND
J11: Qwiic EZO-pH; JST_SH_SM04B-SRSS-TB_1x04-1MP_P1.00mm_Horizontal; MPN SM04B-SRSS-TB(LF)(SN); Digi-Key_PN 455-1804-1-ND
J12: Qwiic EZO-ORP; JST_SH_SM04B-SRSS-TB_1x04-1MP_P1.00mm_Horizontal; MPN SM04B-SRSS-TB(LF)(SN); Digi-Key_PN 455-1804-1-ND
J13: Qwiic EZO-DO; JST_SH_SM04B-SRSS-TB_1x04-1MP_P1.00mm_Horizontal; MPN SM04B-SRSS-TB(LF)(SN); Digi-Key_PN 455-1804-1-ND
J14: Qwiic EZO-RTD; JST_SH_SM04B-SRSS-TB_1x04-1MP_P1.00mm_Horizontal; MPN SM04B-SRSS-TB(LF)(SN); Digi-Key_PN 455-1804-1-ND
J15: Load Cell; TerminalBlock_Phoenix_PT-1,5-4-5.0-H_1x04_P5.00mm_Horizontal; MPN 1757242; Digi-Key_PN 277-1274-ND
J16: RS485 Hamilton; TerminalBlock_Phoenix_PT-1,5-4-5.0-H_1x04_P5.00mm_Horizontal
LED4: Red/Green; LED_0603_1608Metric
R19: 4.7k 1%; R_0402_1005Metric; MPN CRCW04024K70FKED; Digi-Key_PN 541-4.70KLCT-ND
R20: 4.7k 1%; R_0402_1005Metric; MPN CRCW04024K70FKED
R21: 10k; R_0402_1005Metric
R22: 120R DNP; R_0402_1005Metric
R23: 330R; R_0402_1005Metric
R38: 10k 1%; R_0402_1005Metric; MPN CRCW040210K0FKED; Digi-Key_PN 541-10.0KLCT-ND
U14: HX711; SOP-16_4.4x10.4mm_P1.27mm
U15: MAX3485CSA; SOIC-8_3.9x4.9mm_P1.27mm
U21: ISO1541; SOIC-8_3.9x4.9mm_P1.27mm; MPN ISO1541DR
U22: SC16IS740; TSSOP-16_4.4x5mm_P0.65mm; MPN SC16IS740IPW/Q900; Digi-Key_PN 568-13068-1-ND
U23: SN74LVC1G04; SOT-353_SC-70-5; MPN SN74LVC1G04DCKR; Digi-Key_PN 296-11602-1-ND
Y1: 1.8432MHz; Crystal_SMD_HC49-SD; MPN ABLS-1.8432MHZ-B4-T; Digi-Key_PN 535-9930-1-ND

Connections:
/3V3_RAIL: C25.1, C26.1, C33.1, J8.2, J9.2, J10.2, R19.1, R20.1, R21.1, R38.1, U14.1 (VSUP), U14.3 (AVDD), U14.14 (VCC), U15.8 (VCC), U21.1 (VCC1), U22.1 (VDD), U22.8 (I2C/~SPI), U22.14 (~RESET), U23.5 (VCC); also elsewhere on the board
/Digital & I2C/3V3_ISO: J11.2, J12.2, J13.2, J14.2, U21.8 (VCC2)
/Digital & I2C/GND_ISO: J11.1, J12.1, J13.1, J14.1, U21.5 (GND2)
/Digital & I2C/HX711_EN: J15.2, U14.4 (INA-)
/Digital & I2C/HX711_EP: J15.1, U14.5 (INA+)
/Digital & I2C/HX711_SP: J15.3, U14.7 (INB+)
/Digital & I2C/LED_R23_NET: LED4.1 (K), R23.2
/Digital & I2C/RS485_A: J16.1, R22.2, U15.6 (A)
/Digital & I2C/RS485_B: J16.2, R22.1, U15.7 (B)
/Digital & I2C/RS485_DE: U15.2 (~RE), U15.3 (DE), U23.4
/Digital & I2C/RS485_DI: U15.4 (DI), U22.12 (TX)
/Digital & I2C/RS485_RO: U15.1 (RO), U22.13 (RX)
/Digital & I2C/RS485_RTS_N: U22.10 (~RTS), U23.2
/Digital & I2C/SCL_ISO: J11.4, J12.4, J13.4, J14.4, U21.6 (SCL2)
/Digital & I2C/SDA_ISO: J11.3, J12.3, J13.3, J14.3, U21.7 (SDA2)
/Digital & I2C/XTAL1: C31.1, U22.15 (XTAL1), Y1.1
/Digital & I2C/XTAL2: C32.1, U22.16 (XTAL2), Y1.2
/HX711_DOUT: J15.4, R21.2, U14.6 (INB-), U14.12 (DOUT); also elsewhere on the board
/HX711_SCK: U14.10 (XI), U14.13 (PD_SCK); also elsewhere on the board
/I2C_SCL: J8.4, J9.4, J10.4, R20.2, U21.3 (SCL1), U22.5 (SCL/SCLK); also elsewhere on the board
/I2C_SDA: D9.1 (K), J8.3, J9.3, J10.3, R19.2, U21.2 (SDA1), U22.6 (SDA); also elsewhere on the board
/LED_STATUS: R23.1; also elsewhere on the board
/RS485_IRQ: R38.2, U22.7 (~IRQ); also elsewhere on the board
GND: C25.2, C26.2, C31.2, C32.2, C33.2, D9.2 (A), J8.1, J9.1, J10.1, J16.3, J16.4, LED4.2 (A), U14.8 (GND), U14.16 (RATE), U15.5 (GND), U21.4 (GND1), U22.2 (A0/~CS), U22.3 (A1/SI), U22.9 (VSS), U22.11 (~CTS), U23.3 (GND); also elsewhere on the board

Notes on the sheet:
I2C BUS — 400 kHz Fast Mode Pull-ups 4.7k to 3.3V, ESD protection PESD3V3S2USF
HX711 LOAD CELL ADC 24-bit, Gain 128, 80 SPS D2=DOUT, D3=SCK
RS485 MODBUS — Signature only Hamilton TCD + ACD (Incyte/Dencytee) via MAX3485 + SC16IS740 bridge DNP in Essential and Insight
